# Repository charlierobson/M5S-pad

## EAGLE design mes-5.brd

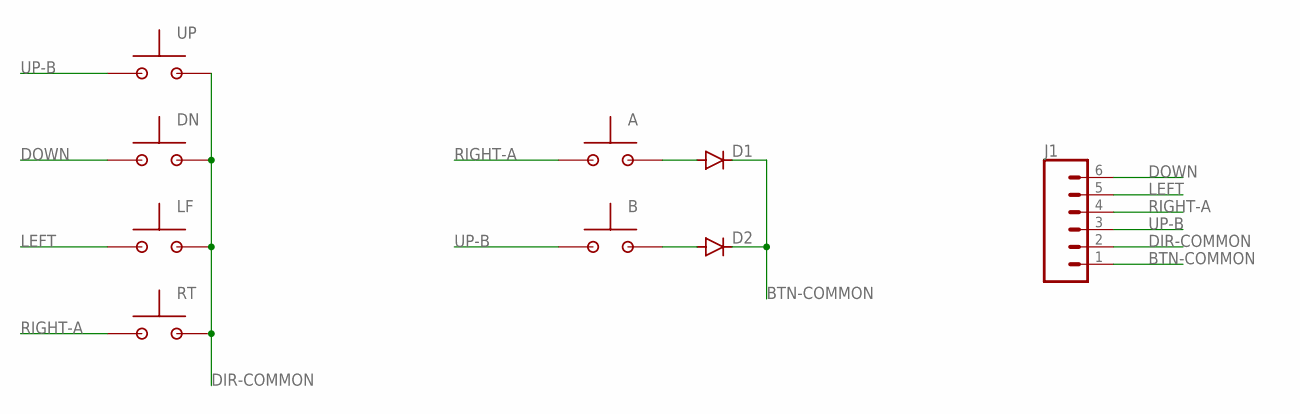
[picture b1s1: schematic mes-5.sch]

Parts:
A: RUBBERBUTTON_CONTACTAREA_9MM
B: RUBBERBUTTON_CONTACTAREA_9MM
D1, D2: 1N4148DO35-7; DO35-7
DN: RUBBERBUTTON_CONTACTAREA_9MM
J1: CONN_06LONGPADS; 1X06_LONGPADS
LF: RUBBERBUTTON_CONTACTAREA_9MM
RT: RUBBERBUTTON_CONTACTAREA_9MM
UP: RUBBERBUTTON_CONTACTAREA_9MM

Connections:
BTN-COMMON: D1.C, D2.C, J1.1
DIR-COMMON: DN.B, J1.2, LF.B, RT.B, UP.B
DOWN: DN.A, J1.6
LEFT: J1.5, LF.A
unnamed: A.B, D1.A
unnamed: B.B, D2.A
RIGHT-A: A.A, J1.4, RT.A
UP-B: B.A, J1.3, UP.A

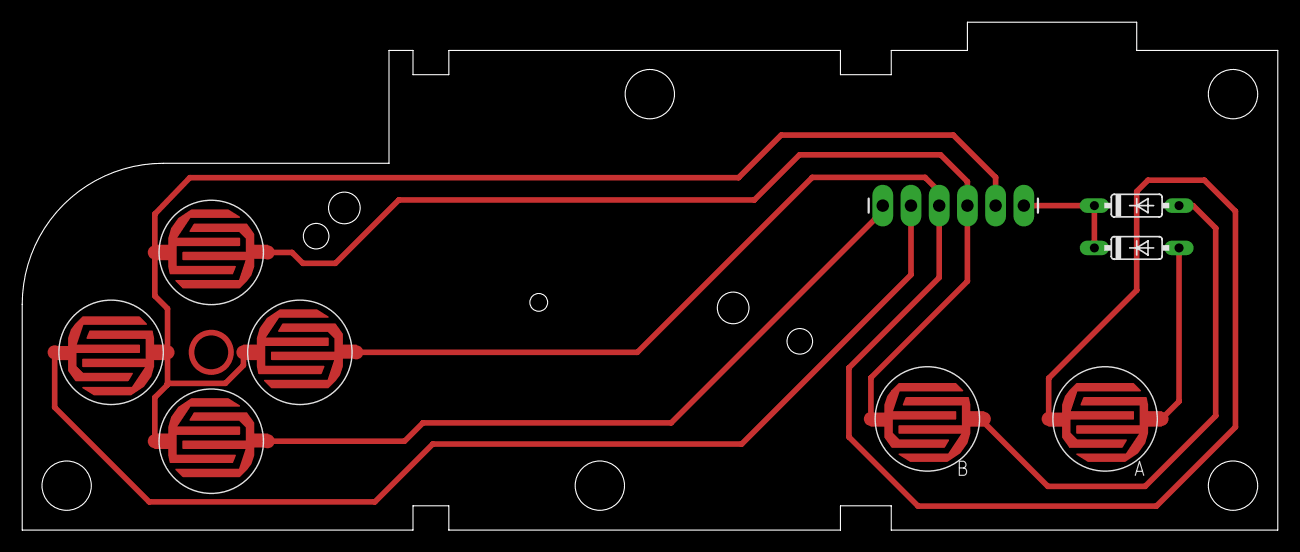
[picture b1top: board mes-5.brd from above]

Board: 2 copper layers, 113.0 x 45.7 mm, 9 parts (0 on the bottom side), 8 nets.

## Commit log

2023-03-23 draft 1

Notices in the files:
parts and their libraries:
SparkFun-Connectors: Licensing: Creative Commons ShareAlike 4.0 International - https://creativecommons.org/licenses/by-sa/4.0
